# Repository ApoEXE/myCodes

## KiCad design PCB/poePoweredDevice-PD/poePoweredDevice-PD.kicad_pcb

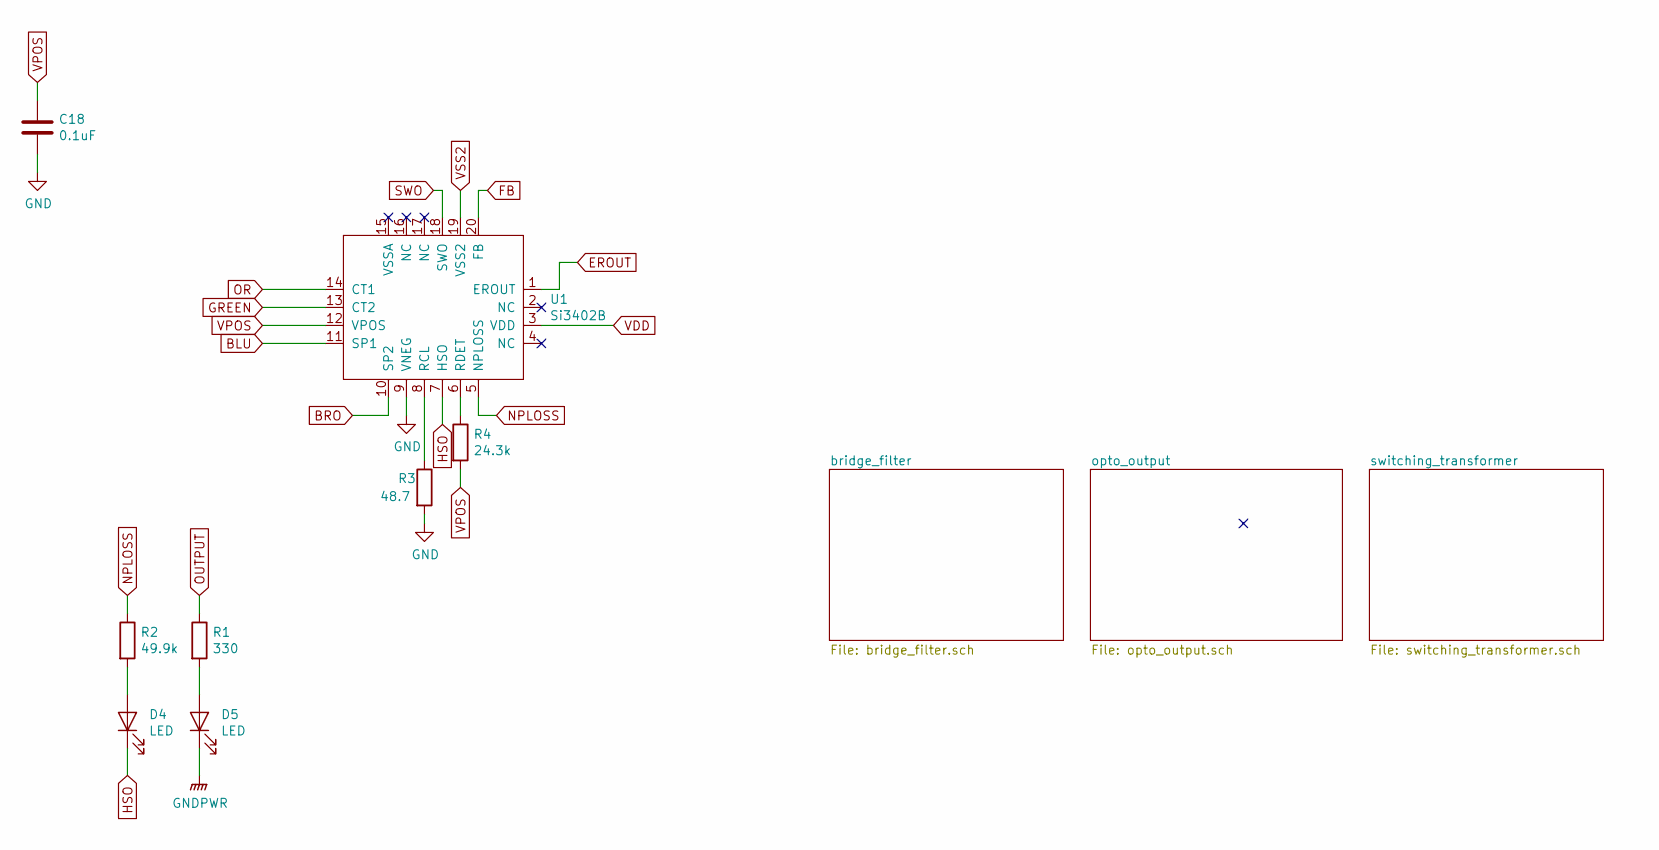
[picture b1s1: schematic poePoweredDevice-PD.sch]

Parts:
C18: 0.1uF; C_0805_2012Metric
D4, D5: LED; D_0603_1608Metric
R1: 330; R_0805_2012Metric
R2: 49.9k; R_0805_2012Metric
R3: 48.7; R_0805_2012Metric
R4: 24.3k; R_0805_2012Metric
U1: Si3402B; QFN-20-1EP_5x5mm_P0.65mm_EP3.35x3.35mm

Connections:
BLU: U1.11 (SP1); also elsewhere on the board
BRO: U1.10 (SP2); also elsewhere on the board
EROUT: U1.1 (EROUT); also elsewhere on the board
FB: C18.1, R4.2, U1.12 (VPOS), U1.20 (FB); also elsewhere on the board
GND: C18.2, R3.2, U1.9 (VNEG); also elsewhere on the board
GNDPWR: D5.1 (K); also elsewhere on the board
GREEN: U1.13 (CT2); also elsewhere on the board
HSO: D4.1 (K), U1.7 (HSO), U1.19 (VSS2); also elsewhere on the board
NPLOSS: R2.1, U1.5 (NPLOSS)
unnamed: D4.2 (A), R2.2
unnamed: D5.2 (A), R1.2
unnamed: R3.1, U1.8 (RCL)
unnamed: R4.1, U1.6 (RDET)
OR: U1.14 (CT1); also elsewhere on the board
OUTPUT: R1.1; also elsewhere on the board
SWO: U1.18 (SWO); also elsewhere on the board
VDD: U1.3 (VDD); also elsewhere on the board

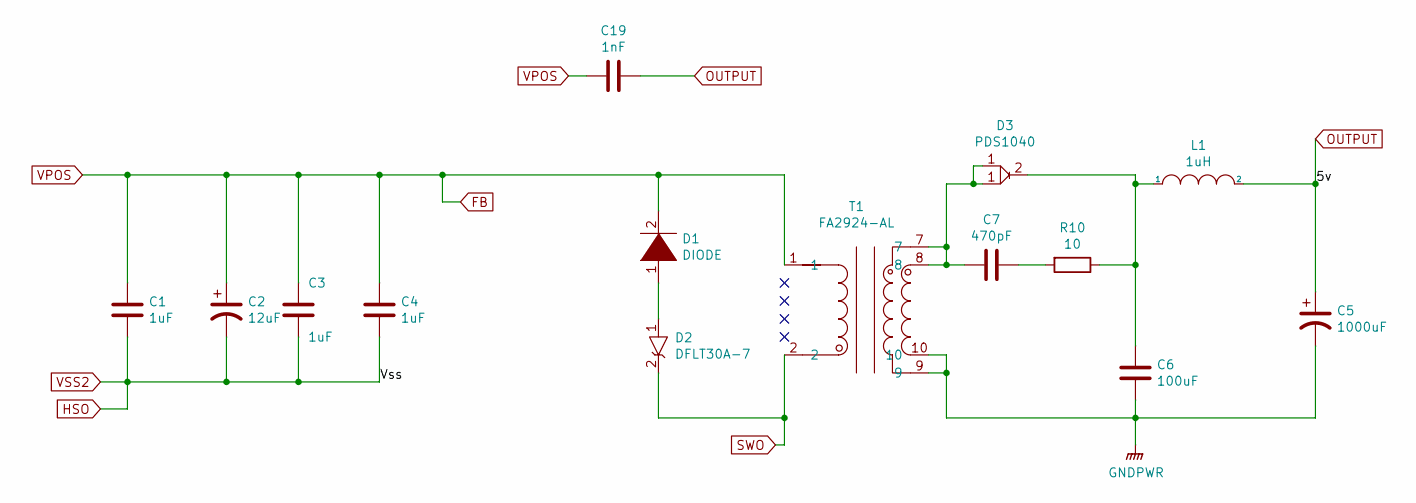
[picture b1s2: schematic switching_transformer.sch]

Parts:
C1, C3, C4: 1uF; C_1210_3225Metric
C2: 12uF; CP_Radial_D6.3mm_P2.50mm
C5: 1000uF; CP_Radial_D8.0mm_P2.50mm
C6: 100uF; C_1210_3225Metric
C7: 470pF; C_0805_2012Metric
C19: 1nF; C_1806_4516Metric_Pad1.57x1.80mm_HandSolder
D1: DIODE; D_SOD-123
D2: DFLT30A-7
D3: PDS1040; POWERDI-5
L1: 1uH; DO1608C-102MLC
R10: 10; R_0805_2012Metric
T1: FA2924-AL; FA2924-ALD

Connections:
FB: C1.1, C2.1, C3.1, C4.1, C19.2, D1.2 (A), T1.1; also elsewhere on the board
GNDPWR: C5.2, C6.2, T1.9, T1.10; also elsewhere on the board
HSO: C1.2, C2.2, C3.2, C4.2; also elsewhere on the board
unnamed: C6.1, D3.2, L1.1, R10.1
unnamed: C7.1, D3.1, T1.7, T1.8
unnamed: C7.2, R10.2
unnamed: D1.1 (K), D2.1
OUTPUT: C5.1, C19.1, L1.2; also elsewhere on the board
SWO: D2.2, T1.2; also elsewhere on the board

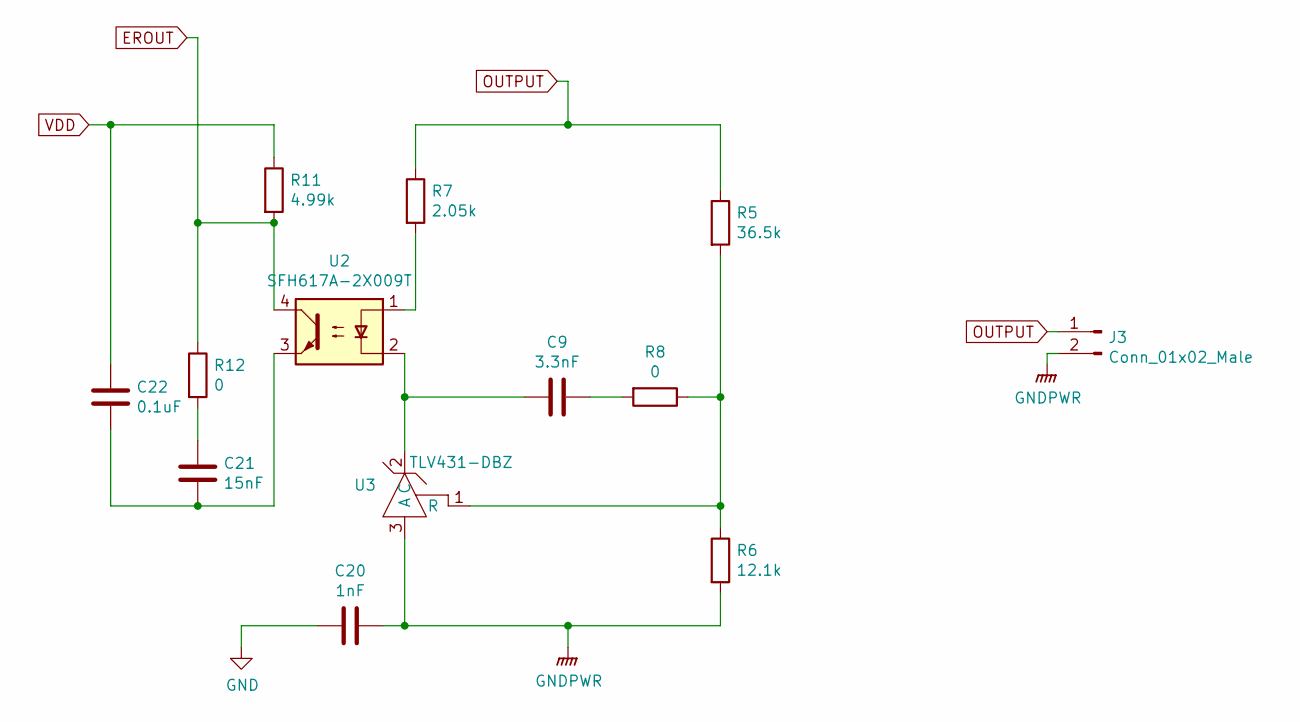
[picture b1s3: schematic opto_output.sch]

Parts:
C9: 3.3nF; C_0805_2012Metric
C20: 1nF; C_1806_4516Metric_Pad1.57x1.80mm_HandSolder
C21: 15nF; C_0805_2012Metric
C22: 0.1uF; C_0805_2012Metric
J3: Conn_01x02_Male; PinHeader_1x02_P2.54mm_Vertical
R5: 36.5k; R_0805_2012Metric
R6: 12.1k; R_0805_2012Metric
R7: 2.05k; R_0603_1608Metric
R8, R12: 0; R_0805_2012Metric
R11: 4.99k; R_0805_2012Metric
U2: SFH617A-2X009T; VO618A-3X017T
U3: TLV431-DBZ; SOT-23

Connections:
EROUT: R11.2, R12.1, U2.4; also elsewhere on the board
GND: C20.2; also elsewhere on the board
GNDPWR: C20.1, J3.2, R6.2, U3.3 (A); also elsewhere on the board
unnamed: C9.1, U2.2, U3.2 (C)
unnamed: C9.2, R8.2
unnamed: C21.1, R12.2
unnamed: C21.2, C22.1, U2.3
unnamed: R5.2, R6.1, R8.1, U3.1 (R)
unnamed: R7.2, U2.1
OUTPUT: J3.1, R5.1, R7.1; also elsewhere on the board
VDD: C22.2, R11.1; also elsewhere on the board

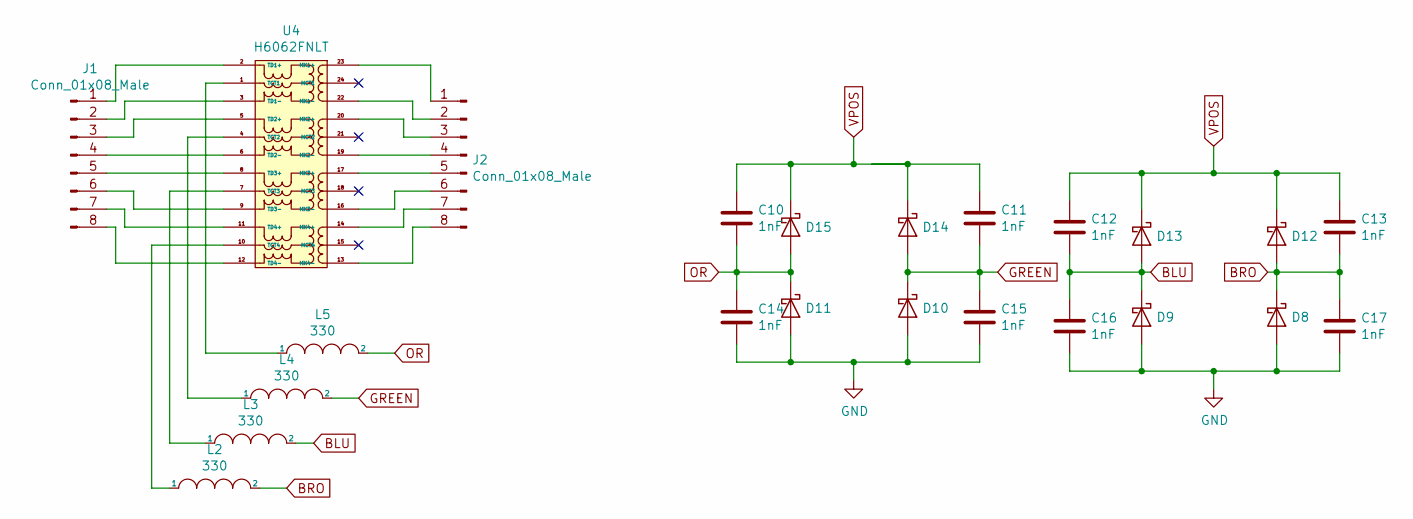
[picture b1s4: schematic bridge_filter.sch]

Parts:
C10, C11, C12, C13, C14, C15, C16, C17: 1nF; C_0603_1608Metric
D8, D9, D10, D11, D12, D13, D14, D15: D_Schottky; D_SMA
J1, J2: Conn_01x08_Male; PinHeader_1x08_P2.54mm_Vertical
L2, L3, L4, L5: 330; L_0805_2012Metric
U4: H6062FNLT; Pulse_H6062FNLT

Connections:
BLU: C12.2, C16.1, D9.1 (K), D13.2 (A), L3.2; also elsewhere on the board
BRO: C13.2, C17.1, D8.1 (K), D12.2 (A), L2.2; also elsewhere on the board
FB: C10.1, C11.1, C12.1, C13.1, D12.1 (K), D13.1 (K), D14.1 (K), D15.1 (K); also elsewhere on the board
GND: C14.2, C15.2, C16.2, C17.2, D8.2 (A), D9.2 (A), D10.2 (A), D11.2 (A); also elsewhere on the board
GREEN: C11.2, C15.1, D10.1 (K), D14.2 (A), L4.2; also elsewhere on the board
unnamed: J1.1, U4.2 (TD1+)
unnamed: J1.2, U4.3 (TD1-)
unnamed: J1.3, U4.5 (TD2+)
unnamed: J1.4, U4.6 (TD2-)
unnamed: J1.5, U4.8 (TD3+)
unnamed: J1.6, U4.9 (TD3-)
unnamed: J1.7, U4.11 (TD4+)
unnamed: J1.8, U4.12 (TD4-)
unnamed: J2.1, U4.23 (MX1+)
unnamed: J2.2, U4.22 (MX1-)
unnamed: J2.3, U4.20 (MX2+)
unnamed: J2.4, U4.19 (MX2-)
unnamed: J2.5, U4.17 (MX3+)
unnamed: J2.6, U4.16 (MX3-)
unnamed: J2.7, U4.14 (MX4+)
unnamed: J2.8, U4.13 (MX4-)
unnamed: L2.1, U4.10 (TCT4)
unnamed: L3.1, U4.7 (TCT3)
unnamed: L4.1, U4.4 (TCT2)
unnamed: L5.1, U4.1 (TCT1)
OR: C10.2, C14.1, D11.1 (K), D15.2 (A), L5.2; also elsewhere on the board

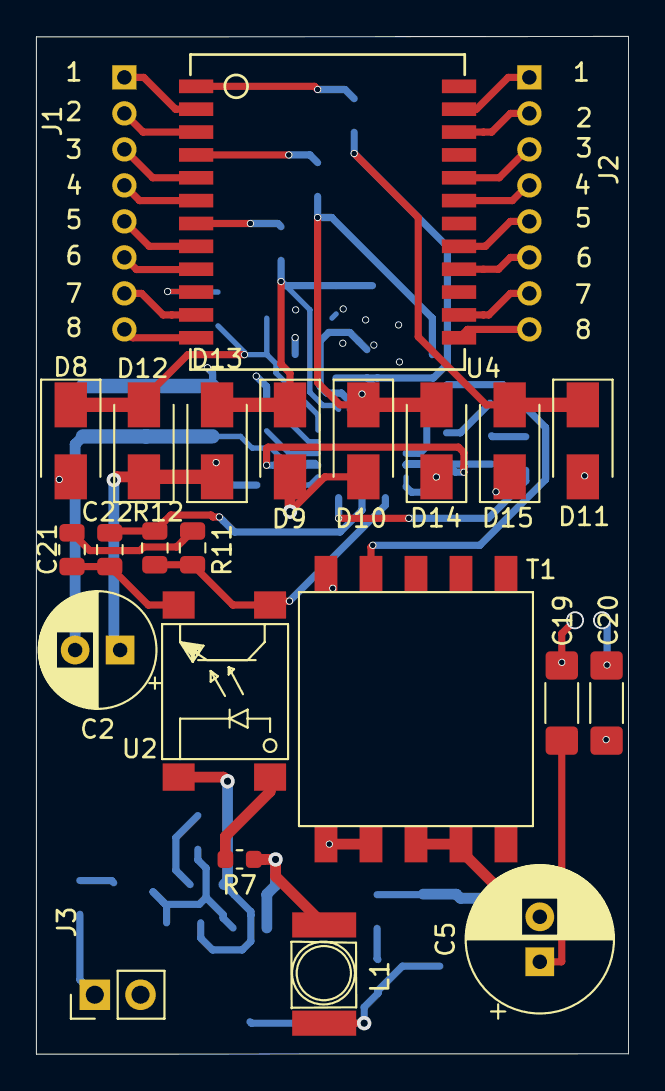
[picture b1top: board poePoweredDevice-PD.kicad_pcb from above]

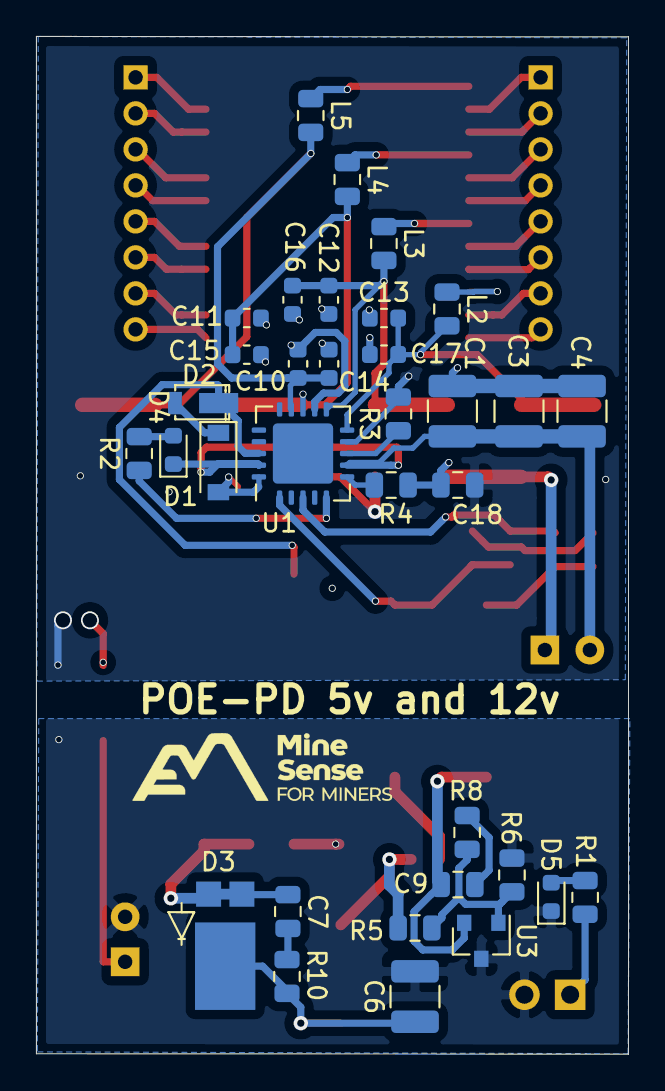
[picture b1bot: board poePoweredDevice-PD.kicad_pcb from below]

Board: 4 copper layers, 32.9 x 56.5 mm, 58 parts (34 on the bottom side), 47 nets.

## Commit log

2020-03-02 my codes for testing
2020-03-02 modified rtplotting
2020-03-03 updating server
2020-03-03 added serial read
2020-03-03 added string headers
2020-03-06 ServiceBroadcaster for starting cmdtpms in CS without gui or android application, corrections in server csvdata proccessing
2020-03-10 trying new stuff angular pro and other stuff
2020-03-16 added some better printing javascript
2020-03-16 half working
2020-03-18 in plotting got javascript working to plot table of 6 sensors, in readSerial, got it to create a unique file for each sensor id with delta calculations
2020-03-18 improving layout myCode and change readSerial to sensorDatalogger
2020-03-18 added config txt file need to fix multiple sensor filtering dinamicly
2020-03-19 working version for unknown sensor monitoring
2020-03-19 added linux service on bootup example
2020-03-19 TK1 fixes ubuntu14 UPSTART added
2020-03-20 finally a first draf of realtime updating sections of webpage, fixed some problema in csvData, this works with Javascript and Ajax
2020-03-20 ssh checked
2020-03-20 added new logs from today
2020-03-24 added line graph
2020-03-25 working version for updating live graph and table
2020-03-28 added border detection
2020-03-31 added MNIST dataset and pytorchP2.py
2020-04-01 uploading all
2020-04-03 finished CNN RNN pt6
2020-04-04 created a fully functional cnn rnn saved the model and uploaded fullcnn.py loading_fullcnn.py
2020-04-05 finish course and graph it
2020-04-06 working version or thermal line detection with canny
2020-05-31 remove heavy files
2020-07-10 improved app.py for graph of tpms andworking on serial com
2020-09-09 deleted tpmscsv and added new startup script
2020-09-10 added changes to sensorDataloggerSerial.py crc checksum
2020-10-05 more codes
2021-03-01 modified android service for new logger of tas
2021-03-16 playing with opengl
2021-03-16 server working ubuntu
2021-03-16 converted to classes for learning
2021-03-16 created a version with separeted classes one object using list initializer one object callfuncions
2021-03-23 fast examples of dnn opencv and opengl implementation
